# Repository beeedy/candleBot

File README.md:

# candleBot

This repository holds the software and firmware for a small palm-sized robot that was designed and fabricated in 4 weeks for the University of St. Thomas' microcontroller course. The goal of the robot was that it would autonomously search a maze for a candle and extinguish the candle. The robot's solution for putting out the candle is to actually 'call the fire department' which was either [Tyler Holmes](https://github.com/TDHolmes) or myself.

It is believed that the hardware files for this robot were lost however work is being done to completely redesign the robot from the ground up over here: [PiBot](https://github.com/TDHolmes/PiBot)

This robot was designed around:
* PIC18F97J94 (Main processor, design requirement)
* [PIXY Cam](http://charmedlabs.com/default/pixy-cmucam5/) (Used to perform rudamentary SLAM)
* [FONA](https://www.adafruit.com/product/1946) (Used to 'call the fire department')
* MC33926PNB (Motor controllers)
* Nintendo Wii IR Cameras (2x, stereo vision used for camera 3D localization)
* PS2 connector (Allowed for PlayStation controllers to be connected and used to drive the bot)

This repo is dormant and there are no future plans to put more work into this project. This project now resides as the first microcontroller project taken on by [Tyler Holmes](https://github.com/TDHolmes) and myself.

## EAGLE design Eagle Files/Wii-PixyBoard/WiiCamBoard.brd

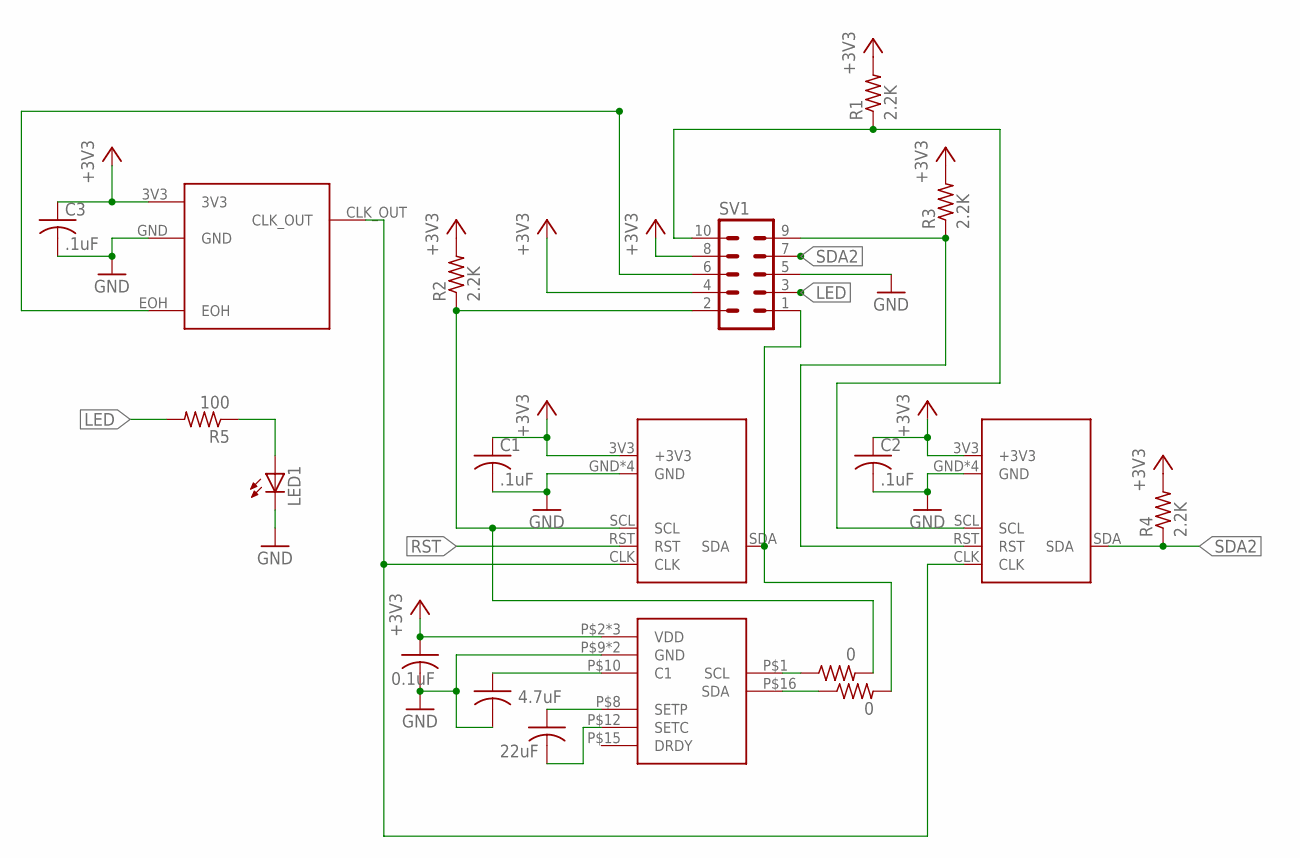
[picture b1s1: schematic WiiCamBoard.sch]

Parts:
C1, C2, C3: .1uF; C0805
C4: 0.1uF; C0805
C5: 4.7uF; C0805
C6: 22uF; C0805
LED1: LED5MM
R1, R2, R3, R4: 2.2K; M0805
R5: 100; M0805
R6, R7: 0; R0805
SV1: MA05-2
U$1, U$2: WII_IR_CAM
U$3: CB3LV-3C
U$4: HMC5883L

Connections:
+3V3: C1.1, C2.1, C3.1, C4.1, R1.2, R2.2, R3.2, R4.2, SV1.4, SV1.8, U$1.3V3 (+3V3), U$2.3V3 (+3V3), U$3.3V3, U$4.P$2 (VDD), U$4.P$4 (VDD), U$4.P$13 (VDD)
CLK: U$1.CLK, U$2.CLK, U$3.CLK_OUT
GND: C1.2, C2.2, C3.2, C4.2, C5.2, LED1.K (C), SV1.5, U$1.GND, U$1.GND2 (GND), U$1.GND3 (GND), U$1.GND4 (GND), U$2.GND, U$2.GND2 (GND), U$2.GND3 (GND), U$2.GND4 (GND), U$3.GND, U$4.P$9 (GND), U$4.P$11 (GND)
LED: R5.2, SV1.3
unnamed: LED1.A, R5.1
unnamed: R6.1, U$4.P$1 (SCL)
unnamed: R7.1, U$4.P$16 (SDA)
unnamed: C6.1, U$4.P$8 (SETP)
unnamed: C6.2, U$4.P$12 (SETC)
unnamed: C5.1, U$4.P$10 (C1)
unnamed: SV1.6, U$3.EOH
RST: R3.1, SV1.9, U$1.RST, U$2.RST
SCL: R2.1, R6.2, SV1.2, U$1.SCL
SCL2: R1.1, SV1.10, U$2.SCL
SDA1: R7.2, SV1.1, U$1.SDA
SDA2: R4.1, SV1.7, U$2.SDA

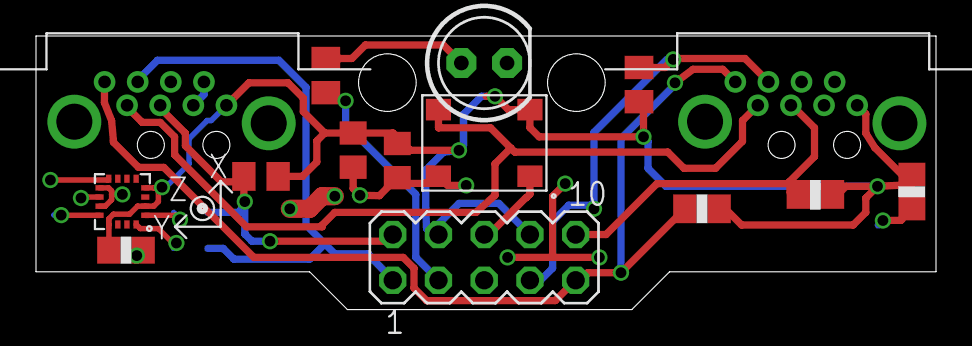
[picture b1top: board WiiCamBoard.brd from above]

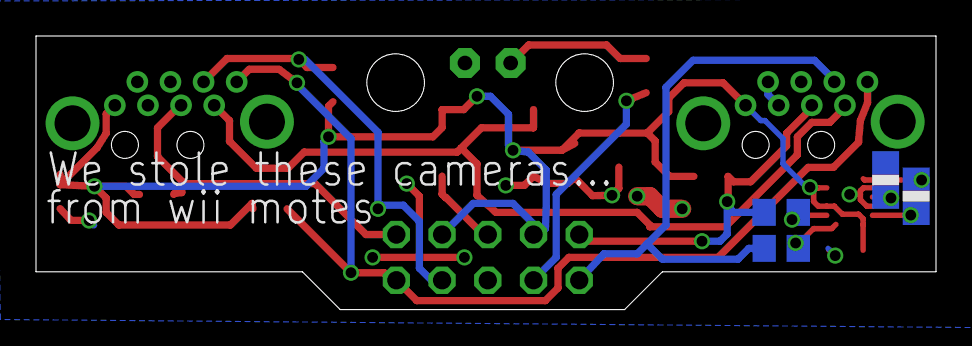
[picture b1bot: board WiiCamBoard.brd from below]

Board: 2 copper layers, 50.0 x 15.2 mm, 19 parts (4 on the bottom side), 16 nets.

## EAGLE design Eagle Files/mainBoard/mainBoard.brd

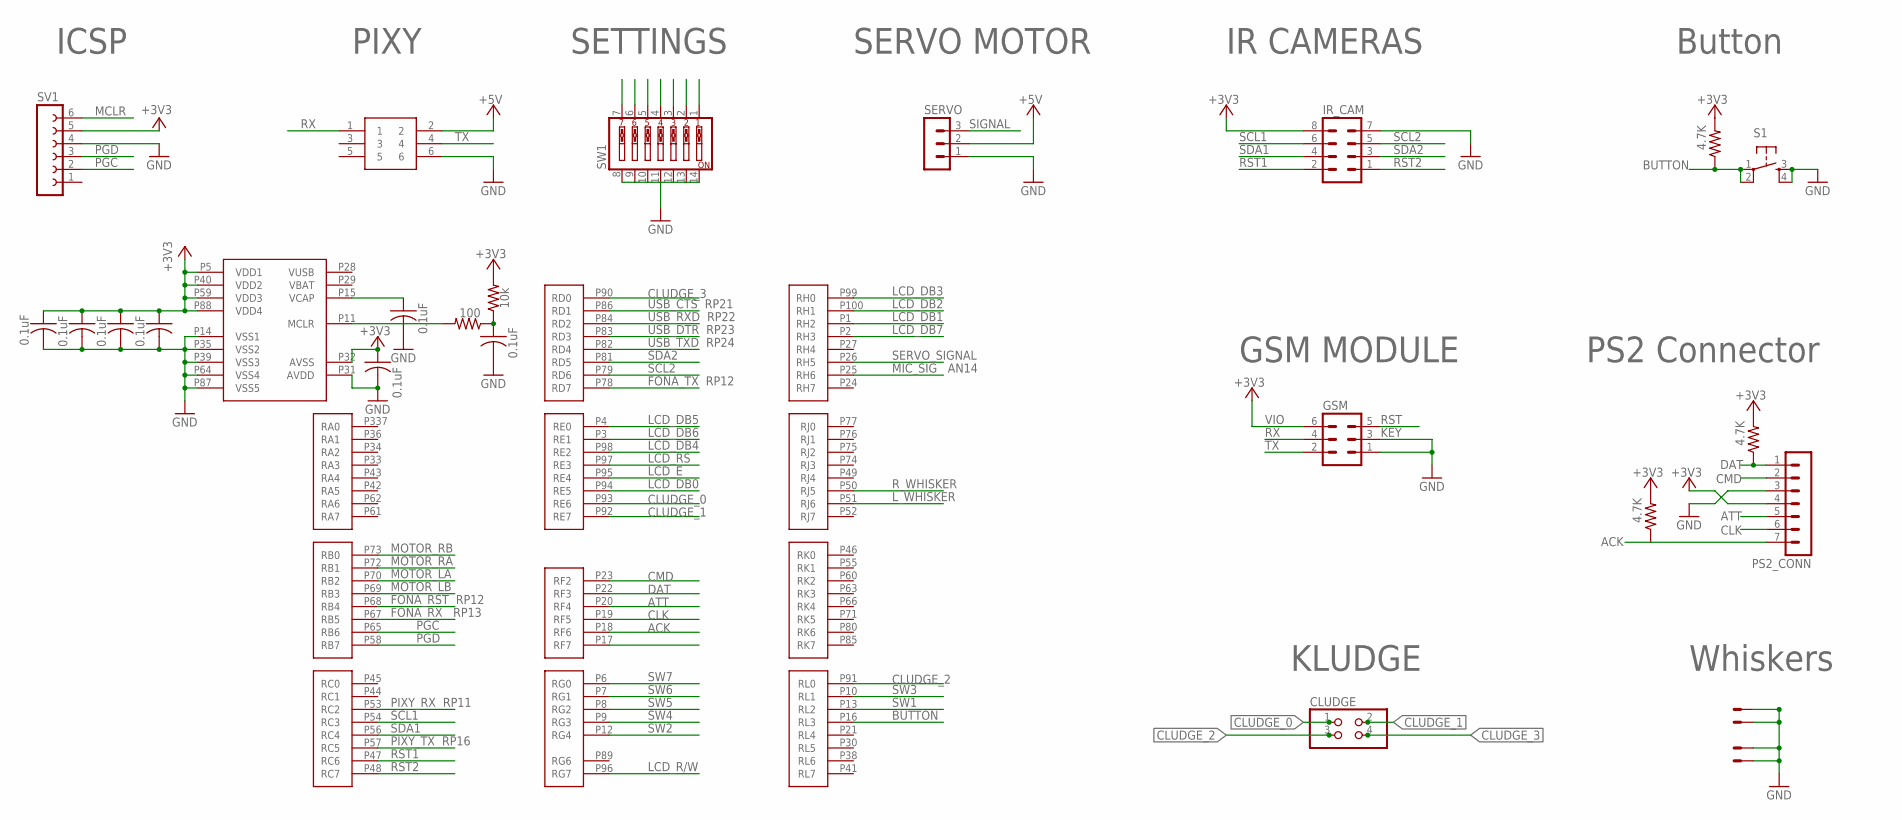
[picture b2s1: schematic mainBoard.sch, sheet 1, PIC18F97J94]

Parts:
C16, C18, C19, C20, C28, C29, C30: 0.1uF; C0805
CLUDGE: PINHD-2X2; 2X02
GSM: MA03-2
IR_CAM: MA04-2
PS2_CONN: MA07-1
R16: 100; R0805
R17: 10k; R0805
R18, R19, R20: 4.7K; M0805
S1: 10-XX; B3F-10XX
SERVO: MA03-1
SV1: FE06-1; FE06
SW1: SW_DIP-7; EDG-07
U$1: PIC18F97J94; QTFP-100
U$15: PIXY; PIXY_HEADER
X1, X2: 22-23-2021

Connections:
+3V3: C16.1, C18.1, C19.1, C20.1, C28.1, GSM.6, IR_CAM.8, PS2_CONN.4, R17.2, R18.2, R19.2, R20.2, SV1.5, U$1.P5 (VDD1), U$1.P32 (AVSS), U$1.P40 (VDD2), U$1.P59 (VDD3), U$1.P88 (VDD4); also elsewhere on the board
+5V: SERVO.2, U$15.2; also elsewhere on the board
ACK: PS2_CONN.7, R20.1, U$1.P18 (RF6)
ATT: PS2_CONN.5, U$1.P20 (RF4)
BUTTON: R18.1, S1.1, S1.2 (P1), U$1.P16 (RL3)
CLK: PS2_CONN.6, U$1.P19 (RF5)
CLUDGE_0: CLUDGE.1, U$1.P93 (RE6)
CLUDGE_1: CLUDGE.2, U$1.P92 (RE7)
CLUDGE_2: CLUDGE.3, U$1.P91 (RL0)
CLUDGE_3: CLUDGE.4, U$1.P90 (RD0)
CMD: PS2_CONN.2, U$1.P23 (RF2)
DAT: PS2_CONN.1, R19.1, U$1.P22 (RF3)
GND: C16.2, C18.2, C19.2, C20.2, C28.2, C29.2, C30.2, GSM.1, GSM.3, IR_CAM.7, PS2_CONN.3, S1.3 (S), S1.4 (S1), SERVO.1, SV1.4, SW1.8, SW1.9, SW1.10, SW1.11, SW1.12, SW1.13, SW1.14, U$1.P14 (VSS1), U$1.P31 (AVDD), U$1.P35 (VSS2), U$1.P39 (VSS3), U$1.P64 (VSS4), U$1.P87 (VSS5), U$15.6, X1.1, X1.2, X2.1, X2.2; also elsewhere on the board
GSM_RST: GSM.5, U$1.P68 (RB4)
GSM_RX: GSM.4, U$1.P67 (RB5)
GSM_TX: GSM.2, U$1.P78 (RD7)
I2C_SCL: IR_CAM.6, U$1.P79 (RD6); also elsewhere on the board
I2C_SCL1: IR_CAM.5, U$1.P54 (RC3)
I2C_SDA: IR_CAM.4, U$1.P81 (RD5); also elsewhere on the board
I2C_SDA1: IR_CAM.3, U$1.P56 (RC4)
LCD_DB0: U$1.P94 (RE5); also elsewhere on the board
LCD_DB1: U$1.P1 (RH2); also elsewhere on the board
LCD_DB2: U$1.P100 (RH1); also elsewhere on the board
LCD_DB3: U$1.P99 (RH0); also elsewhere on the board
LCD_DB4: U$1.P98 (RE2); also elsewhere on the board
LCD_DB5: U$1.P4 (RE0); also elsewhere on the board
LCD_DB6: U$1.P3 (RE1); also elsewhere on the board
LCD_DB7: U$1.P2 (RH3); also elsewhere on the board
LCD_E: U$1.P95 (RE4); also elsewhere on the board
LCD_R/W: U$1.P96 (RG7); also elsewhere on the board
LCD_RS: U$1.P97 (RE3); also elsewhere on the board
L_WHISKER: U$1.P51 (RJ6)
MCLR: R16.2, SV1.6, U$1.P11 (MCLR)
MIC_SIG: U$1.P25 (RH6); also elsewhere on the board
MOTOR_LA: U$1.P70 (RB2); also elsewhere on the board
MOTOR_LB: U$1.P69 (RB3); also elsewhere on the board
MOTOR_RA: U$1.P72 (RB1); also elsewhere on the board
MOTOR_RB: U$1.P73 (RB0); also elsewhere on the board
unnamed: C29.1, U$1.P15 (VCAP)
unnamed: C30.1, R16.1, R17.1
PGC: SV1.2, U$1.P65 (RB6)
PGD: SV1.3, U$1.P58 (RB7)
PIXY_RX: U$1.P53 (RC2), U$15.1
PIXY_TX: U$1.P57 (RC5), U$15.4
RST1: IR_CAM.2, U$1.P47 (RC6)
RST2: IR_CAM.1, U$1.P48 (RC7)
R_WHISKER: U$1.P50 (RJ5)
SERVO_SIGNAL: SERVO.3, U$1.P26 (RH5)
SW1: SW1.1, U$1.P13 (RL2)
SW2: SW1.2, U$1.P12 (RG4)
SW3: SW1.3, U$1.P10 (RL1)
SW4: SW1.4, U$1.P9 (RG3)
SW5: SW1.5, U$1.P8 (RG2)
SW6: SW1.6, U$1.P7 (RG1)
SW7: SW1.7, U$1.P6 (RG0)
USB_CTS: U$1.P86 (RD1); also elsewhere on the board
USB_DTR: U$1.P83 (RD3); also elsewhere on the board
USB_RXD: U$1.P84 (RD2); also elsewhere on the board
USB_TXD: U$1.P82 (RD4); also elsewhere on the board

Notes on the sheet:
LCD_DB5
LCD_DB6
LCD_DB7
LCD_DB1
LCD_DB2
LCD_DB3
LCD_DB4
LCD_RS
LCD_R/W
LCD_E
LCD_DB0
MCLR
PGD
PGC
USB_CTS RP21
USB_RXD RP22
USB_DTR RP23
USB_TXD RP24
MIC_SIG AN14
SW7
SW6
SW5
SW4
SW3
SW2
SW1
SDA2
SCL2
MOTOR_RB
MOTOR_RA
MOTOR_LA
MOTOR_LB
PIXY_TX RP16
PIXY_RX RP11
PIXY
SETTINGS
ICSP
IR CAMERAS
SCL1
SDA1

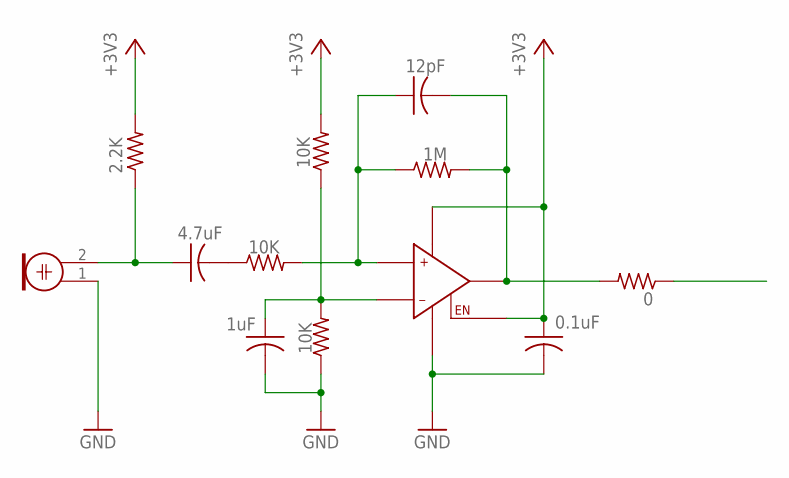
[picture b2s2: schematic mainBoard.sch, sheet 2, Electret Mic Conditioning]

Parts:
C11: 1uF; C0805
C12: 4.7uF; C0805
C13: 12pF; C0805
C14: 0.1uF; C0805
M1: ELECTRET_MICROPHON-WM-63PR; WM-63PR
R1, R5, R6: 10K; R0805
R2: 1M; R0805
R4: 2.2K; R0805
R7: 0; R0805
U$4: OPA334

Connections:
+3V3: C14.1, R4.2, R5.2, U$4.P$5 (EN), U$4.P$6 (V+); also elsewhere on the board
GND: C11.2, C14.2, M1.1, R6.1, U$4.P$2 (V-); also elsewhere on the board
MIC_SIG: R7.1; also elsewhere on the board
unnamed: C12.2, R1.1
unnamed: C12.1, M1.2, R4.1
unnamed: C13.1, R1.2, R2.1, U$4.P$3 (IN+)
unnamed: C11.1, R5.1, R6.2, U$4.P$4 (IN-)
unnamed: C13.2, R2.2, R7.2, U$4.P$1 (VOUT)

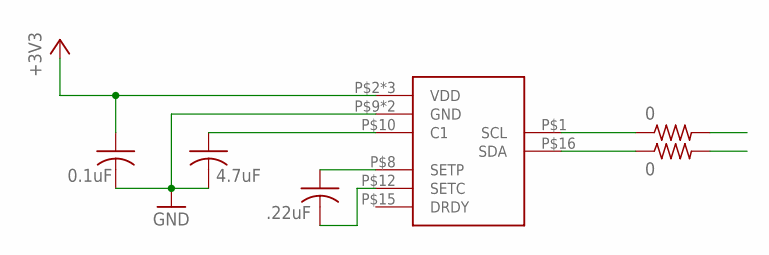
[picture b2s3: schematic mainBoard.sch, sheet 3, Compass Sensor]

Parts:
C8: .22uF; C0805
C9: 4.7uF; C0805
C10: 0.1uF; C0805
R8, R9: 0; R0805
U$3: HMC5883L

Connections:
+3V3: C10.1, U$3.P$2 (VDD), U$3.P$4 (VDD), U$3.P$13 (VDD); also elsewhere on the board
GND: C9.2, C10.2, U$3.P$9 (GND), U$3.P$11 (GND); also elsewhere on the board
I2C_SCL: R8.2; also elsewhere on the board
I2C_SDA: R9.2; also elsewhere on the board
unnamed: C8.1, U$3.P$8 (SETP)
unnamed: C8.2, U$3.P$12 (SETC)
unnamed: C9.1, U$3.P$10 (C1)
unnamed: R8.1, U$3.P$1 (SCL)
unnamed: R9.1, U$3.P$16 (SDA)

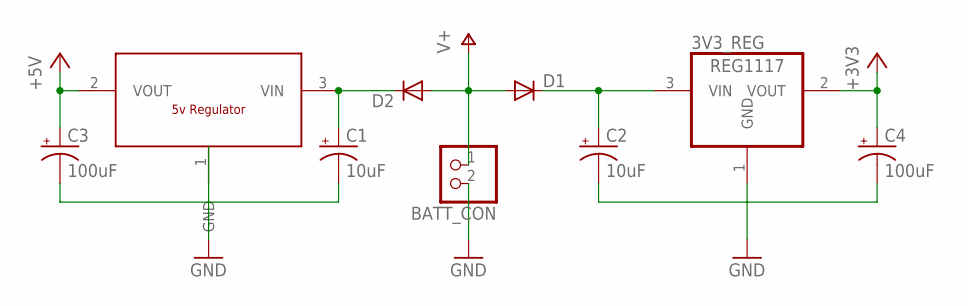
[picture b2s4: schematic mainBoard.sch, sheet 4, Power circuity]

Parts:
3V3_REG: REG1117; SOT223
5V_REG: NCP1117-DPAK; DPAK-2
BATT_CON: JST_2PIN-THM; JST-PH-2-THM
C1, C2: 10uF; UD-4X5,8_NICHICON
C3, C4: 100uF; UD-6,3X5,8_NICHICON
D1, D2: DIODE-SOD123; SOD123

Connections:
+3V3: 3V3_REG.2 (VOUT), C4.+; also elsewhere on the board
+5V: 5V_REG.2 (VOUT), C3.+; also elsewhere on the board
GND: 3V3_REG.1 (GND), 5V_REG.1 (GND), BATT_CON.2 (1), C1.-, C2.-, C3.-, C4.-; also elsewhere on the board
unnamed: 5V_REG.3 (VIN), C1.+, D2.C
unnamed: 3V3_REG.3 (VIN), C2.+, D1.C
V+: BATT_CON.1 (2), D1.A, D2.A; also elsewhere on the board

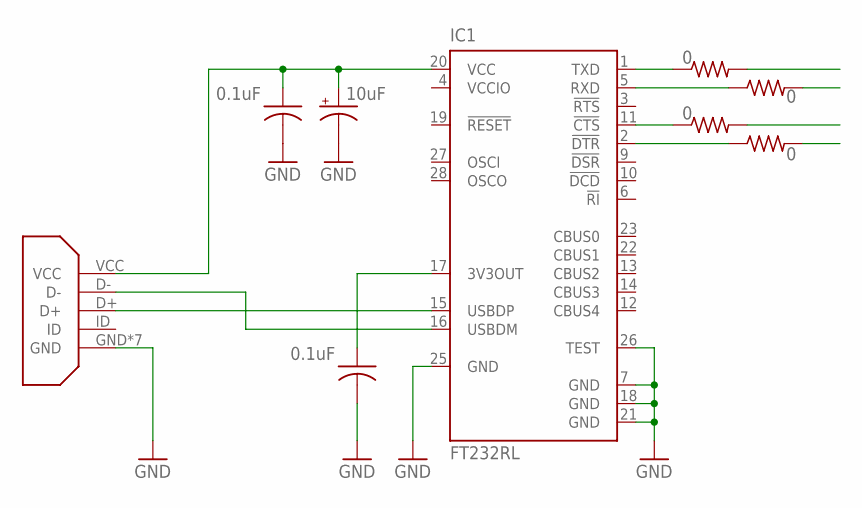
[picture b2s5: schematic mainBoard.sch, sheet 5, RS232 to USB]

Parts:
C5, C7: 0.1uF; C0805
C6: 10uF; UD-4X5,8_NICHICON
IC1: FT232RL; SSOP28
R10, R11, R12, R13: 0; R0805
U$2: MICRO_USB; MICRO_USB_FCI

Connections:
GND: C5.2, C6.-, C7.2, IC1.7 (GND), IC1.18 (GND), IC1.21 (GND), IC1.25 (GND), IC1.26 (TEST), U$2.GND, U$2.GND1 (GND), U$2.GND2 (GND), U$2.P$1 (GND), U$2.P$2 (GND), U$2.P$3 (GND), U$2.P$4 (GND); also elsewhere on the board
unnamed: IC1.1 (TXD), R10.1
unnamed: IC1.5 (RXD), R11.1
unnamed: IC1.11 (!CTS), R12.1
unnamed: IC1.2 (!DTR), R13.1
unnamed: IC1.16 (USBDM), U$2.D-
unnamed: IC1.15 (USBDP), U$2.D+
unnamed: C5.1, IC1.17 (3V3OUT)
unnamed: C6.+, C7.1, IC1.20 (VCC), U$2.VCC
USB_CTS: R12.2; also elsewhere on the board
USB_DTR: R13.2; also elsewhere on the board
USB_RXD: R11.2; also elsewhere on the board
USB_TXD: R10.2; also elsewhere on the board
VCCIO: IC1.4 (VCCIO)

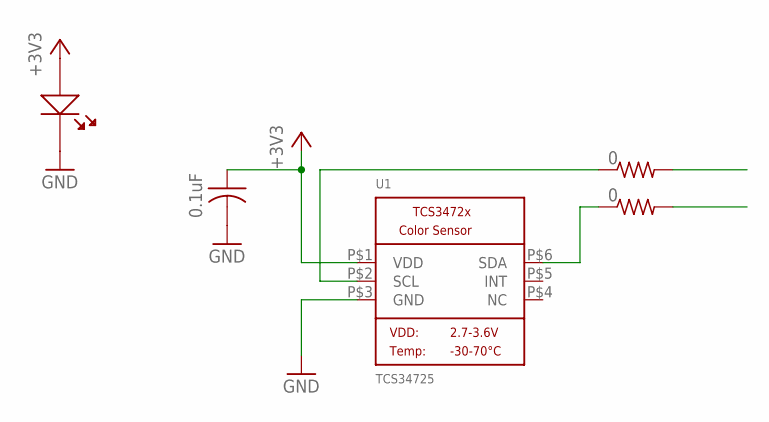
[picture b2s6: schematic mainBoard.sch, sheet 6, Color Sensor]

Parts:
C15: 0.1uF; C0805
R14, R15: 0; R0805
U1: TCS34725; TCS3472_FN6
U$5: LED

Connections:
+3V3: C15.1, U1.P$1 (VDD), U$5.ANODE; also elsewhere on the board
GND: C15.2, U1.P$3 (GND), U$5.CATHODE; also elsewhere on the board
I2C_SCL: R15.2; also elsewhere on the board
I2C_SDA: R14.2; also elsewhere on the board
unnamed: R15.1, U1.P$2 (SCL)
unnamed: R14.1, U1.P$6 (SDA)

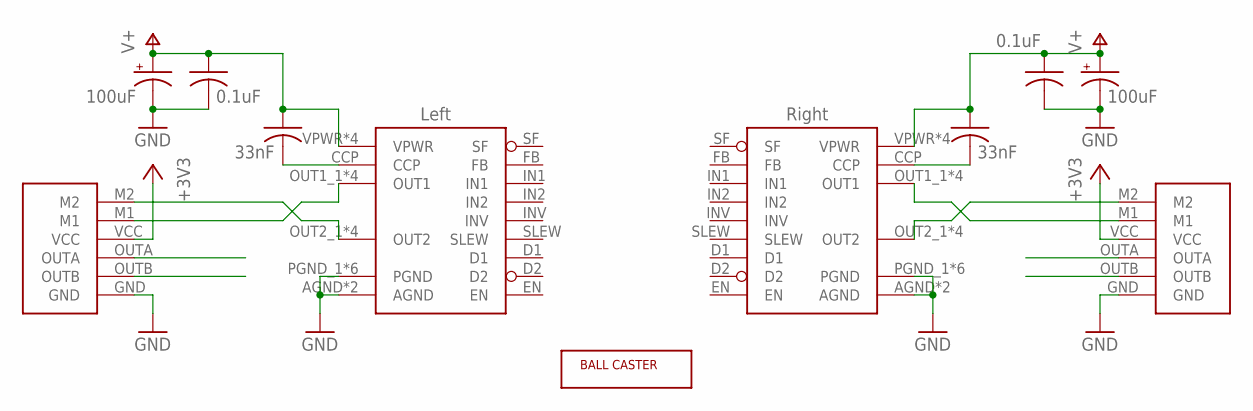
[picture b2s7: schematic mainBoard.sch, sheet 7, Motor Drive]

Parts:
C22, C25: 33nF; C0805
C23, C26: 0.1uF; C0805
C24, C27: 100uF; UD-4X5,8_NICHICON
U$7: POLOLU_BALLCASTER; CASTER
U$8, U$9: POLOLU_MOTORDRIVE; MOTOR
U$10, U$11: MOTORDRIVE; PQFN

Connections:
+3V3: U$8.VCC, U$9.VCC; also elsewhere on the board
GND: C23.2, C24.-, C26.2, C27.-, U$8.GND, U$9.GND, U$10.AGND, U$10.AGND_L (AGND), U$10.PGND_1 (PGND), U$10.PGND_2 (PGND), U$10.PGND_3 (PGND), U$10.PGND_4 (PGND), U$10.PGND_5 (PGND), U$10.PGND_6 (PGND), U$11.AGND, U$11.AGND_L (AGND), U$11.PGND_1 (PGND), U$11.PGND_2 (PGND), U$11.PGND_3 (PGND), U$11.PGND_4 (PGND), U$11.PGND_5 (PGND), U$11.PGND_6 (PGND); also elsewhere on the board
MOTOR_LA: U$8.OUTA; also elsewhere on the board
MOTOR_LB: U$8.OUTB; also elsewhere on the board
MOTOR_RA: U$9.OUTA; also elsewhere on the board
MOTOR_RB: U$9.OUTB; also elsewhere on the board
unnamed: C22.2, U$10.CCP
unnamed: U$8.M1, U$10.OUT1_1 (OUT1), U$10.OUT1_2 (OUT1), U$10.OUT1_3 (OUT1), U$10.OUT1_4 (OUT1)
unnamed: C25.2, U$11.CCP
unnamed: U$8.M2, U$10.OUT2_1 (OUT2), U$10.OUT2_2 (OUT2), U$10.OUT2_3 (OUT2), U$10.OUT2_4 (OUT2)
unnamed: U$9.M2, U$11.OUT2_1 (OUT2), U$11.OUT2_2 (OUT2), U$11.OUT2_3 (OUT2), U$11.OUT2_4 (OUT2)
unnamed: U$9.M1, U$11.OUT1_1 (OUT1), U$11.OUT1_2 (OUT1), U$11.OUT1_3 (OUT1), U$11.OUT1_4 (OUT1)
V+: C22.1, C23.1, C24.+, C25.1, C26.1, C27.+, U$10.VPWR, U$10.VPWR1 (VPWR), U$10.VPWR2 (VPWR), U$10.VPWR_2 (VPWR), U$11.VPWR, U$11.VPWR1 (VPWR), U$11.VPWR2 (VPWR), U$11.VPWR_2 (VPWR); also elsewhere on the board

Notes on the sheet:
Left
Right

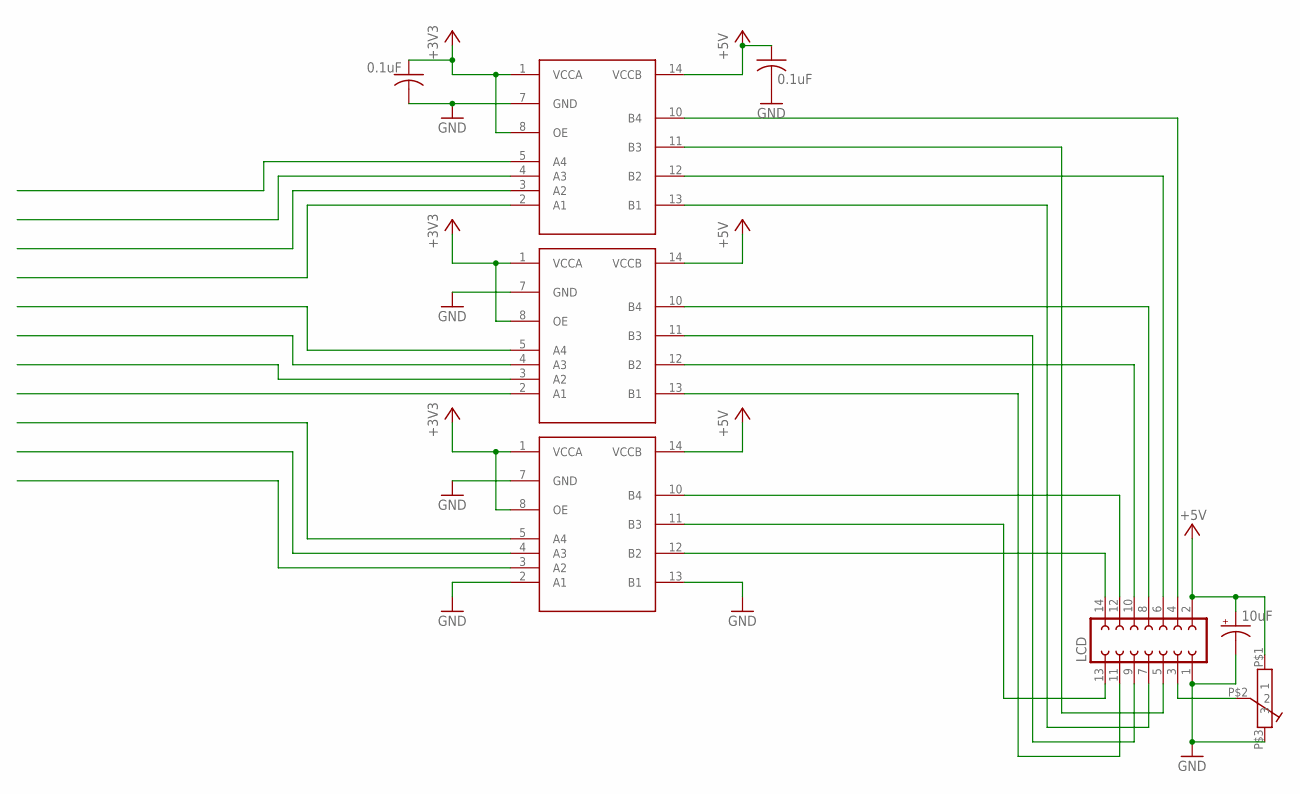
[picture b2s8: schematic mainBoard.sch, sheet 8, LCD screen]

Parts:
10UF: 10uF; UD-4X5,8_NICHICON
C17, C21: 0.1uF; C0805
LCD: FE07-2
U$6: PVG3G-SMD-TRIMMER; PVG3G-SMT-TRIMMER
U$12, U$13, U$14: TXB0104; S-PVQFN-N14

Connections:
+3V3: C17.1, U$12.1 (VCCA), U$12.8 (OE), U$13.1 (VCCA), U$13.8 (OE), U$14.1 (VCCA), U$14.8 (OE); also elsewhere on the board
+5V: 10UF.+, C21.1, LCD.2, U$6.P$1 (1), U$12.14 (VCCB), U$13.14 (VCCB), U$14.14 (VCCB); also elsewhere on the board
GND: 10UF.-, C17.2, C21.2, LCD.1, U$6.P$3 (3), U$12.7 (GND), U$13.7 (GND), U$14.2 (A1), U$14.7 (GND), U$14.13 (B1); also elsewhere on the board
LCD_DB0: U$12.2 (A1); also elsewhere on the board
LCD_DB1: U$13.5 (A4); also elsewhere on the board
LCD_DB2: U$13.4 (A3); also elsewhere on the board
LCD_DB3: U$13.3 (A2); also elsewhere on the board
LCD_DB4: U$13.2 (A1); also elsewhere on the board
LCD_DB5: U$14.5 (A4); also elsewhere on the board
LCD_DB6: U$14.4 (A3); also elsewhere on the board
LCD_DB7: U$14.3 (A2); also elsewhere on the board
LCD_E: U$12.3 (A2); also elsewhere on the board
LCD_R/W: U$12.4 (A3); also elsewhere on the board
LCD_RS: U$12.5 (A4); also elsewhere on the board
unnamed: LCD.3, U$6.P$2 (2)
unnamed: LCD.4, U$12.10 (B4)
unnamed: LCD.5, U$12.11 (B3)
unnamed: LCD.6, U$12.12 (B2)
unnamed: LCD.7, U$12.13 (B1)
unnamed: LCD.8, U$13.10 (B4)
unnamed: LCD.9, U$13.11 (B3)
unnamed: LCD.10, U$13.12 (B2)
unnamed: LCD.11, U$13.13 (B1)
unnamed: LCD.12, U$14.10 (B4)
unnamed: LCD.13, U$14.11 (B3)
unnamed: LCD.14, U$14.12 (B2)

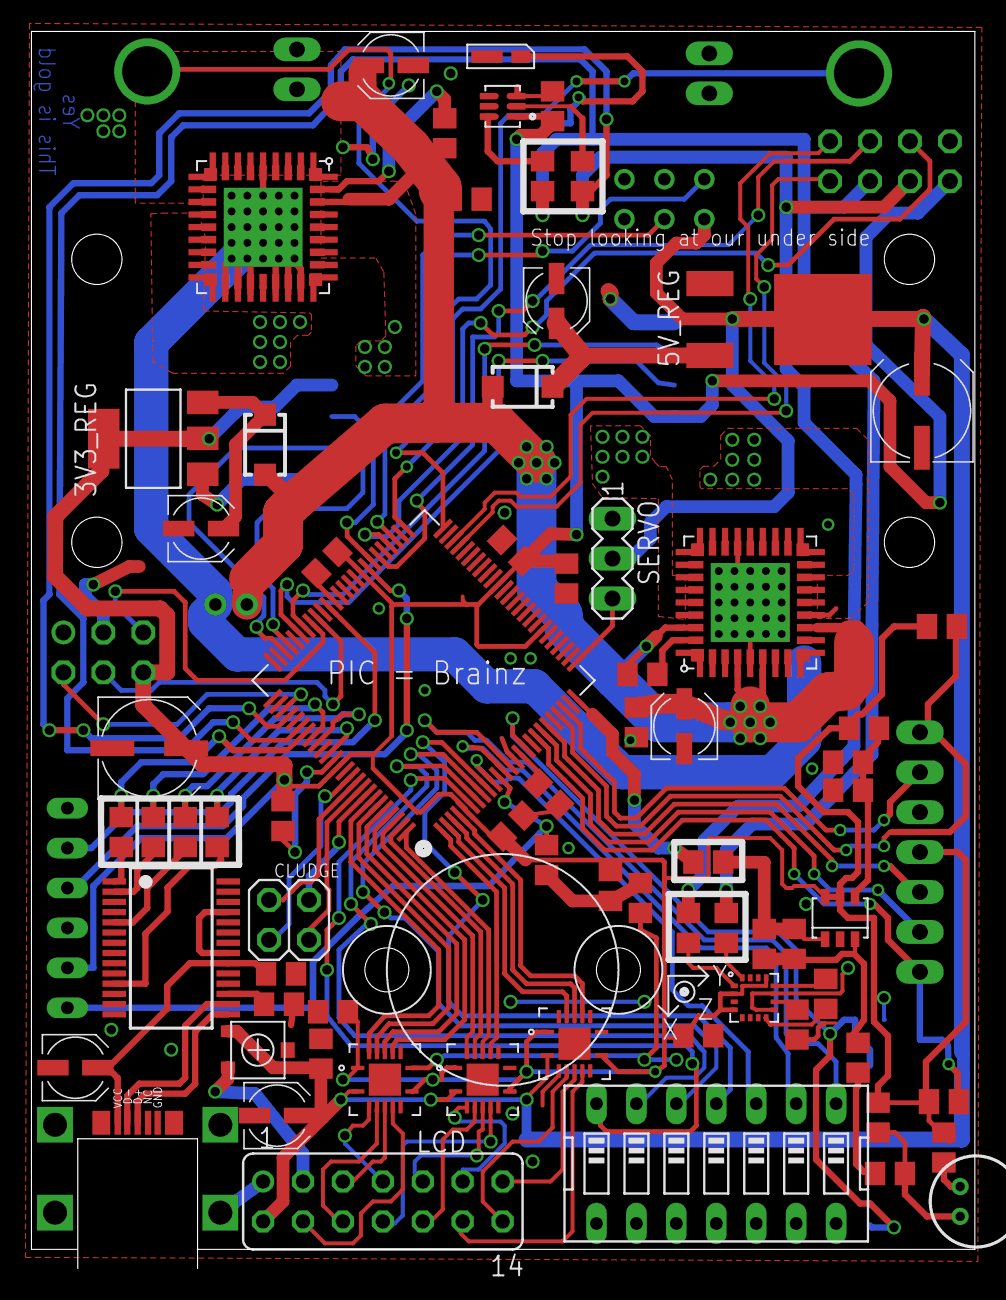
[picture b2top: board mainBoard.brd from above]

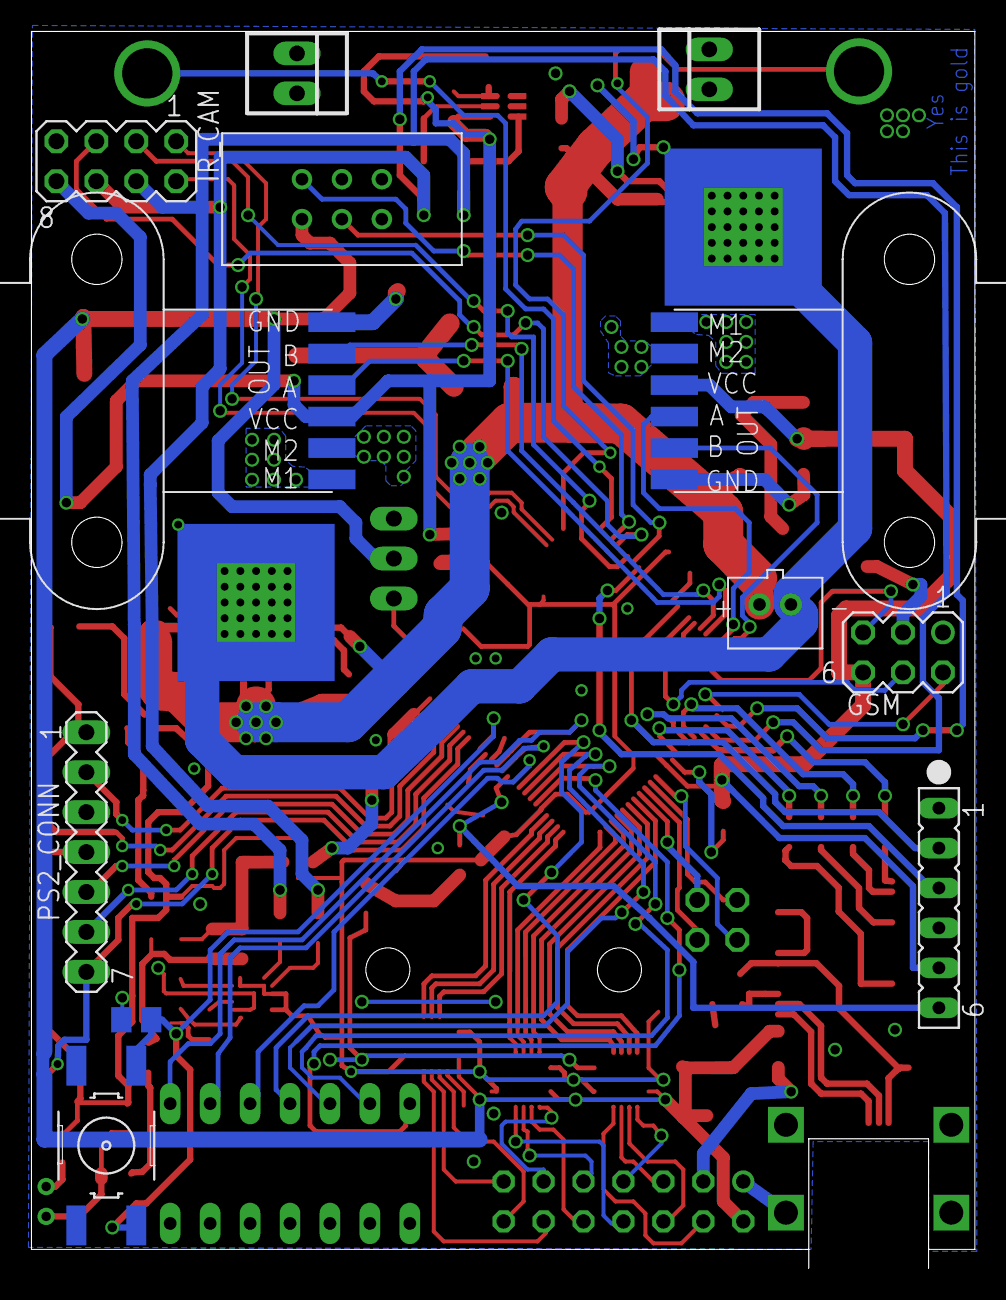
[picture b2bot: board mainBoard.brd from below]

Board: 2 copper layers, 60.0 x 78.7 mm, 84 parts (12 on the bottom side), 98 nets.

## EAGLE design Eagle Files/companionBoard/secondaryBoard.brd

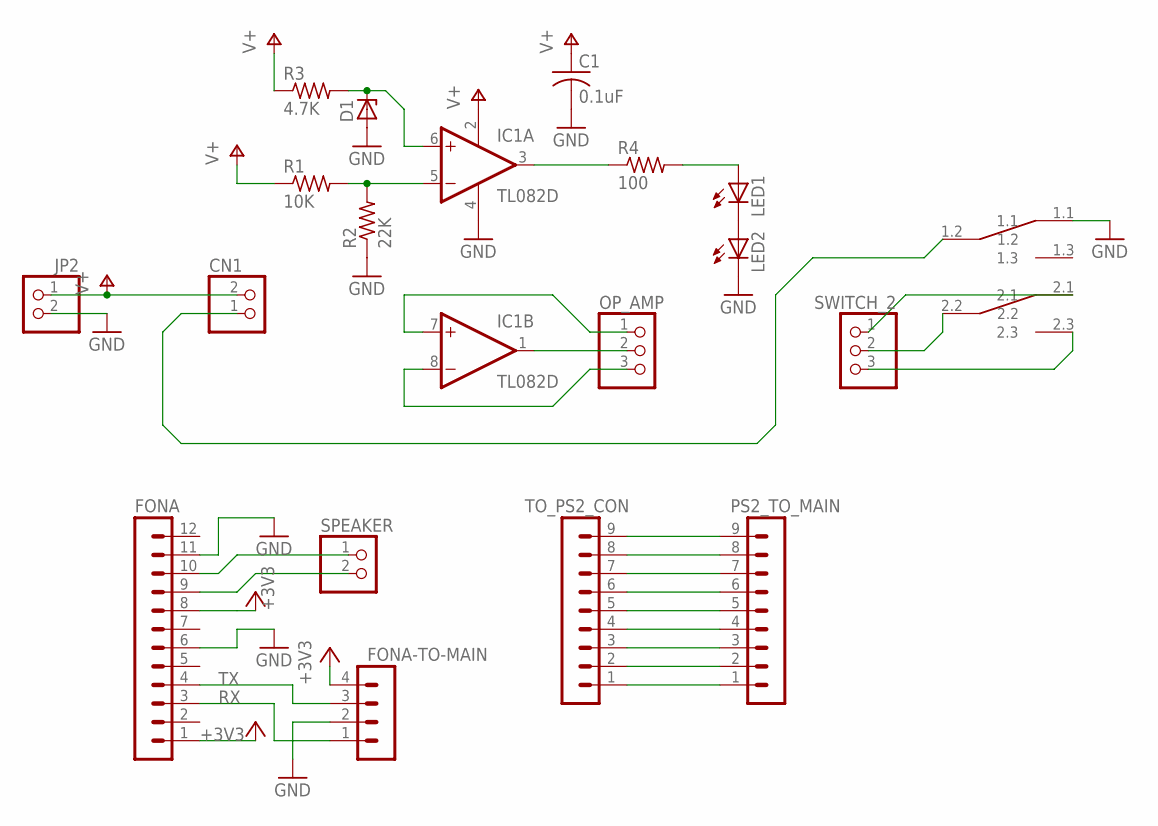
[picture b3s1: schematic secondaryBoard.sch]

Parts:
C1: 0.1uF; C0805
CN1: JST_2PIN-THM; JST-PH-2-THM
D1: ZENER-DIODEZD-5; ZDIO-5
FONA: MA12-1
FONA-TO-MAIN: MA04-1
IC1: TL082D; SO08
JP2: PINHD-1X2/90; 1X02/90
LED1, LED2: LED5MM
OP_AMP: PINHD-1X3CB; 1X03-CLEANBIG
PS2_TO_MAIN: MA09-1
R1: 10K; R0805
R2: 22K; R0805
R3: 4.7K; R0805
R4: 100; R0805
SPEAKER: PINHD-1X2/90; 1X02/90
SWITCH_2: PINHD-1X3CB; 1X03-CLEANBIG
TO_PS2_CON: MA09-1
U$1: DPDT_8.5A

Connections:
+3V3: FONA.1, FONA.8, FONA-TO-MAIN.4
GND: C1.2, D1.A, FONA.6, FONA.11, FONA-TO-MAIN.2, IC1.4 (V-), JP2.2, LED2.K (C), R2.1, U$1.1.1
unnamed: PS2_TO_MAIN.9, TO_PS2_CON.9
unnamed: PS2_TO_MAIN.8, TO_PS2_CON.8
unnamed: PS2_TO_MAIN.7, TO_PS2_CON.7
unnamed: PS2_TO_MAIN.6, TO_PS2_CON.6
unnamed: PS2_TO_MAIN.5, TO_PS2_CON.5
unnamed: PS2_TO_MAIN.4, TO_PS2_CON.4
unnamed: PS2_TO_MAIN.3, TO_PS2_CON.3
unnamed: PS2_TO_MAIN.2, TO_PS2_CON.2
unnamed: PS2_TO_MAIN.1, TO_PS2_CON.1
unnamed: FONA.10, SPEAKER.1
unnamed: FONA.9, SPEAKER.2
unnamed: CN1.1 (2), U$1.1.2
unnamed: R1.2, R2.2
unnamed: LED1.K (C), LED2.A
unnamed: SWITCH_2.1, U$1.2.1
unnamed: SWITCH_2.3, U$1.2.3
unnamed: SWITCH_2.2, U$1.2.2
unnamed: D1.C, IC1.6 (+IN), R3.2
unnamed: IC1.3 (OUT), R4.1
unnamed: LED1.A, R4.2
unnamed: IC1.7 (+IN), OP_AMP.1
unnamed: IC1.1 (OUT), OP_AMP.2
unnamed: IC1.8 (-IN), OP_AMP.3
RX: FONA.3, FONA-TO-MAIN.1
TX: FONA.4, FONA-TO-MAIN.3
V+: C1.1, CN1.2 (1), IC1.2 (V+), JP2.1, R1.1, R3.1

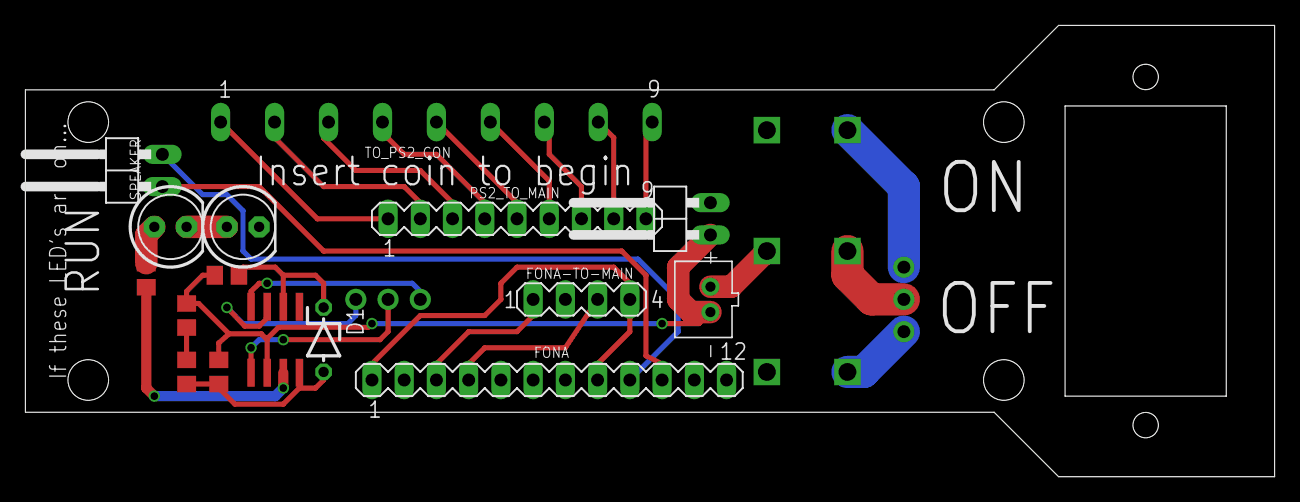
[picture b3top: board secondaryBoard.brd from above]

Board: 2 copper layers, 98.4 x 35.6 mm, 19 parts (0 on the bottom side), 28 nets.

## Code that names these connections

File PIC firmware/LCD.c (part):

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#define mode_4bit 1
#define mode_8bit 2

#define LCD_DB0 PORTEbits.RE5
#define LCD_DB1 PORTHbits.RH2
#define LCD_DB2 PORTHbits.RH1
#define LCD_DB3 PORTHbits.RH0
#define LCD_DB4 PORTEbits.RE2 /* RF2 */
#define LCD_DB5 PORTEbits.RE0 /* RF4 */
#define LCD_DB6 PORTEbits.RE1 /* RF5 */
#define LCD_DB7 PORTHbits.RH5 /* RF6 */
#define LCD_E   PORTEbits.RE4 /* RF3 */
#define LCD_RS  PORTDbits.RD0 /* RD0 */
#define LCD_RW  PORTGbits.RG7

#define LCD_write8bit(data_in) \
    {\
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    CPEN = 0;
    LCDA = 0;

    LCD_DB4 = 0;      // LCD DB4
    LCD_DB5 = 0;      // LCD DB5
    LCD_DB6 = 0;      // LCD DB6
    LCD_DB7 = 0;      // LCD DB7

    LCD_E = 0;      // LCD E
    LCD_RS = 0;      // LCD RS
    LCD_RW = 0;      // LCD R/W


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    delay_init();
    delay_ms(100);

    LCD_RS = 0;
    LCD_RW = 0;

    ////////////////////// Function Set //////////////////////
    delay_long();
    LCD_E = 1;
    LCD_write4bit(0x3);
    delay_long();
    LCD_E = 0;

    delay_ms(50); // 50

    ////////////////////// Function Set //////////////////////
    delay_long();
    LCD_E = 1;
    LCD_write4bit(0x3);
    delay_long();
    LCD_E = 0;

    delay_ms(50); // 50

    ////////////////////// Function Set //////////////////////
    delay_long();
    LCD_E = 1;
    LCD_write4bit(0x3);
    delay_long();
    LCD_E = 0;

    delay_ms(50); // 50

    //////////////////// 4-bit interface ////////////////////
    delay_long();
    LCD_E = 1;
    LCD_write4bit(0x2);
    delay_long();
    LCD_E = 0;

    delay_ms(5); // 5

    ///////////////// font and # of lines  /////////////////
    delay_long();
    LCD_E = 1;
    LCD_write4bit(0x2);
    delay_long();
    LCD_E = 0;

    delay_long();
    LCD_E = 1;
    LCD_write4bit(0x8);
    delay_long();
    LCD_E = 0;

    ///////////////// cursor and disp on  /////////////////
    delay_long();
    LCD_E = 1;
    LCD_write4bit(0x0);
    delay_long();
    LCD_E = 0;

    delay_long();
    LCD_E = 1;
    LCD_write4bit(0xF);
    delay_long();
    LCD_E = 0;

    /////////////////// clear display  ///////////////////
    delay_long();
    LCD_E = 1;
    LCD_write4bit(0x0);
    delay_long();
    LCD_E = 0;

    delay_long();
    LCD_E = 1;
    LCD_write4bit(0x1);
    delay_long();
    LCD_E = 0;

    //////////////// increment on write  ////////////////
    delay_long();
    LCD_E = 1;
    LCD_write4bit(0x0);
    delay_long();
    LCD_E = 0;

    delay_long();
    LCD_E = 1;
    LCD_write4bit(0x6);
    delay_long();
    LCD_E = 0;
    
}

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    ANSEL18 = 0;    //configure H2 as digital I/O
    ANSEL19 = 0;    //configure H3 as digital I/O

    LCD_DB0 = 0;    // LCD DB0
    LCD_DB1 = 0;    // LCD DB1
    LCD_DB2 = 0;    // LCD DB2
    LCD_DB3 = 0;    // LCD DB3
    LCD_DB4 = 0;    // LCD DB4
    LCD_DB5 = 0;    // LCD DB5
    LCD_DB6 = 0;    // LCD DB6
    LCD_DB7 = 0;    // LCD DB7

    LCD_E = 0;      // LCD E
    LCD_RS = 0;     // LCD RS
    LCD_RW = 0;     // LCD R/W


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    delay_init();
    delay_ms(100);

    LCD_RS = 0;
    LCD_RW = 0;

    ////////////////////// Function Set //////////////////////
    delay_short();
    LCD_E = 1;
    LCD_write4bit(0x3);
    delay_long();
    LCD_E = 0;

    delay_ms(50);

    ////////////////////// Function Set //////////////////////
    delay_short();
    LCD_E = 1;
    LCD_write4bit(0x3);
    delay_long();
    LCD_E = 0;

    delay_ms(50);

    ////////////////////// Function Set //////////////////////
    delay_short();
    LCD_E = 1;
    LCD_write4bit(0x3);
    delay_long();
    LCD_E = 0;

    delay_us(100);
    
    ////////////////////// line # and font /////////////////////
    delay_short();
    LCD_E = 1;
    LCD_write8bit(0x28);
    delay_long();
    LCD_E = 0;

    //////////////////// cursor and disp on ////////////////////
    delay_short();
    LCD_E = 1;
    LCD_write8bit(0x08);
    delay_long();
    LCD_E = 0;
    
    ////////////////////// clear display //////////////////////
    delay_short();
    LCD_E = 1;
    LCD_write8bit(0x01);
    delay_long();
    LCD_E = 0;

    /////////////////// increment on write ///////////////////
    delay_short();
    LCD_E = 1;
    LCD_write8bit(0x06);
    delay_long();
    LCD_E = 0;
}

void LCD_placeCursor(char x, char y)
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    {
        case mode_4bit:
            delay_long();
            LCD_E = 1;
            LCD_write4bit(0x80 + (address >> 4));
            delay_long();
            LCD_E = 0;

            delay_long();
            LCD_E = 1;
            LCD_write4bit((address & 0x0F));
            delay_long();
            LCD_E = 0;
            break;

        case mode_8bit:
            delay_short();
            LCD_E = 1;
            LCD_write8bit(address);
            delay_long();
            LCD_E = 0;
            break;
    }
}
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        else
        {
            delay_ms(2);
            LCD_RS = 1;

            switch(mode)
            {
                case mode_4bit:
                    delay_long();
                    LCD_E = 1;
                    LCD_write4bit((string[i] >> 4));
                    delay_long();
                    LCD_E = 0;

                    delay_long();
                    LCD_E = 1;
                    LCD_write4bit((string[i] & 0x0F));
                    delay_long();
                    LCD_E = 0;
                    break;

                case mode_8bit:
                    delay_short();
                    LCD_E = 1;
                    LCD_write8bit(string[i]);
                    delay_long();
                    LCD_E = 0;
                    break;
            }
            delay_ms(2);
            LCD_RS = 0;
        }
    }
}
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    {
        case mode_4bit:
            delay_short();
            LCD_E = 1;
            LCD_write4bit(0x0);
            delay_long();
            LCD_E = 0;

            delay_short();
            LCD_E = 1;
            LCD_write4bit(0x1);
            delay_long();
            LCD_E = 0;
            break;

        case mode_8bit:
            delay_short();
            LCD_E = 1;
            LCD_write8bit(0x01);
            delay_long();
            LCD_E = 0;
            break;
    }
}
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
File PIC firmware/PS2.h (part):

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#define PSAB_CROSS       15
#define PSAB_SQUARE      16

#define CMD PORTFbits.RF2
#define DAT PORTFbits.RF3
#define ATT PORTFbits.RF6
#define CLK PORTFbits.RF5

#define SET(x,y) (x|=(1<<y))
#define CLR(x,y) (x&=(~(1<<y)))
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
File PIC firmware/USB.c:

/*
 * File:   LCD.c
 * Author: TylerHolmes
 *
 * Created on April 11, 2015, 3:00 PM
 *
 * Pins:
 *
 * TXD - RD4 (RP24)
 * RXD - RD2 (RP22)
 * CTS - RD1 (RP21) - Active Low
 *      Clear To Send Control Input / Handshake Signal.
 * DTR - RD3 (RP23) - Active Low
 *      Data Terminal Ready Control Output / Handshake Signal.
 *
 * UART interface support for 7 or 8 data bits,
 * 1 or 2 stop bits and odd / even / mark / space / no parity
 *
 */

#include "USB.h"

#define USB_RX PORTDbits.RD2
#define USB_TX PORTCbits.RC3
#define USB_CTS PORTDbits.RD1
#define USB_DTR PORTDbits.RD3


void USB_Init() {
    
    TRISDbits.TRISD2 = 0;   // Configures RX to an output (transmit from PIC)
    TRISCbits.TRISC3 = 1;   // Configures TX to an input (PIC Recieves)

    TRISDbits.TRISD1 = 1;   // Tristate CTS (Don't need to use)
    TRISDbits.TRISD3 = 1;   // Tristate DTR (Don't need to use)

    // UART must be initialized as well in the main
}

void USB_Read() {

    
}

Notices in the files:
PIC firmware/PS2.h:
Copyright (c) 2015 Broderick Carlin & Tyler Holmes
README.md:
License: MIT
parts and their libraries:
microbuilder: This work is placed in the public domain, and may be freely used for commercial and non-commercial work with the following conditions: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
